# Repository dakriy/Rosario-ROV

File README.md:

# Rosario-ROV
This project is to create a working ROV with features such as live video for the WWU Rosario Beach Marine Laboratory.

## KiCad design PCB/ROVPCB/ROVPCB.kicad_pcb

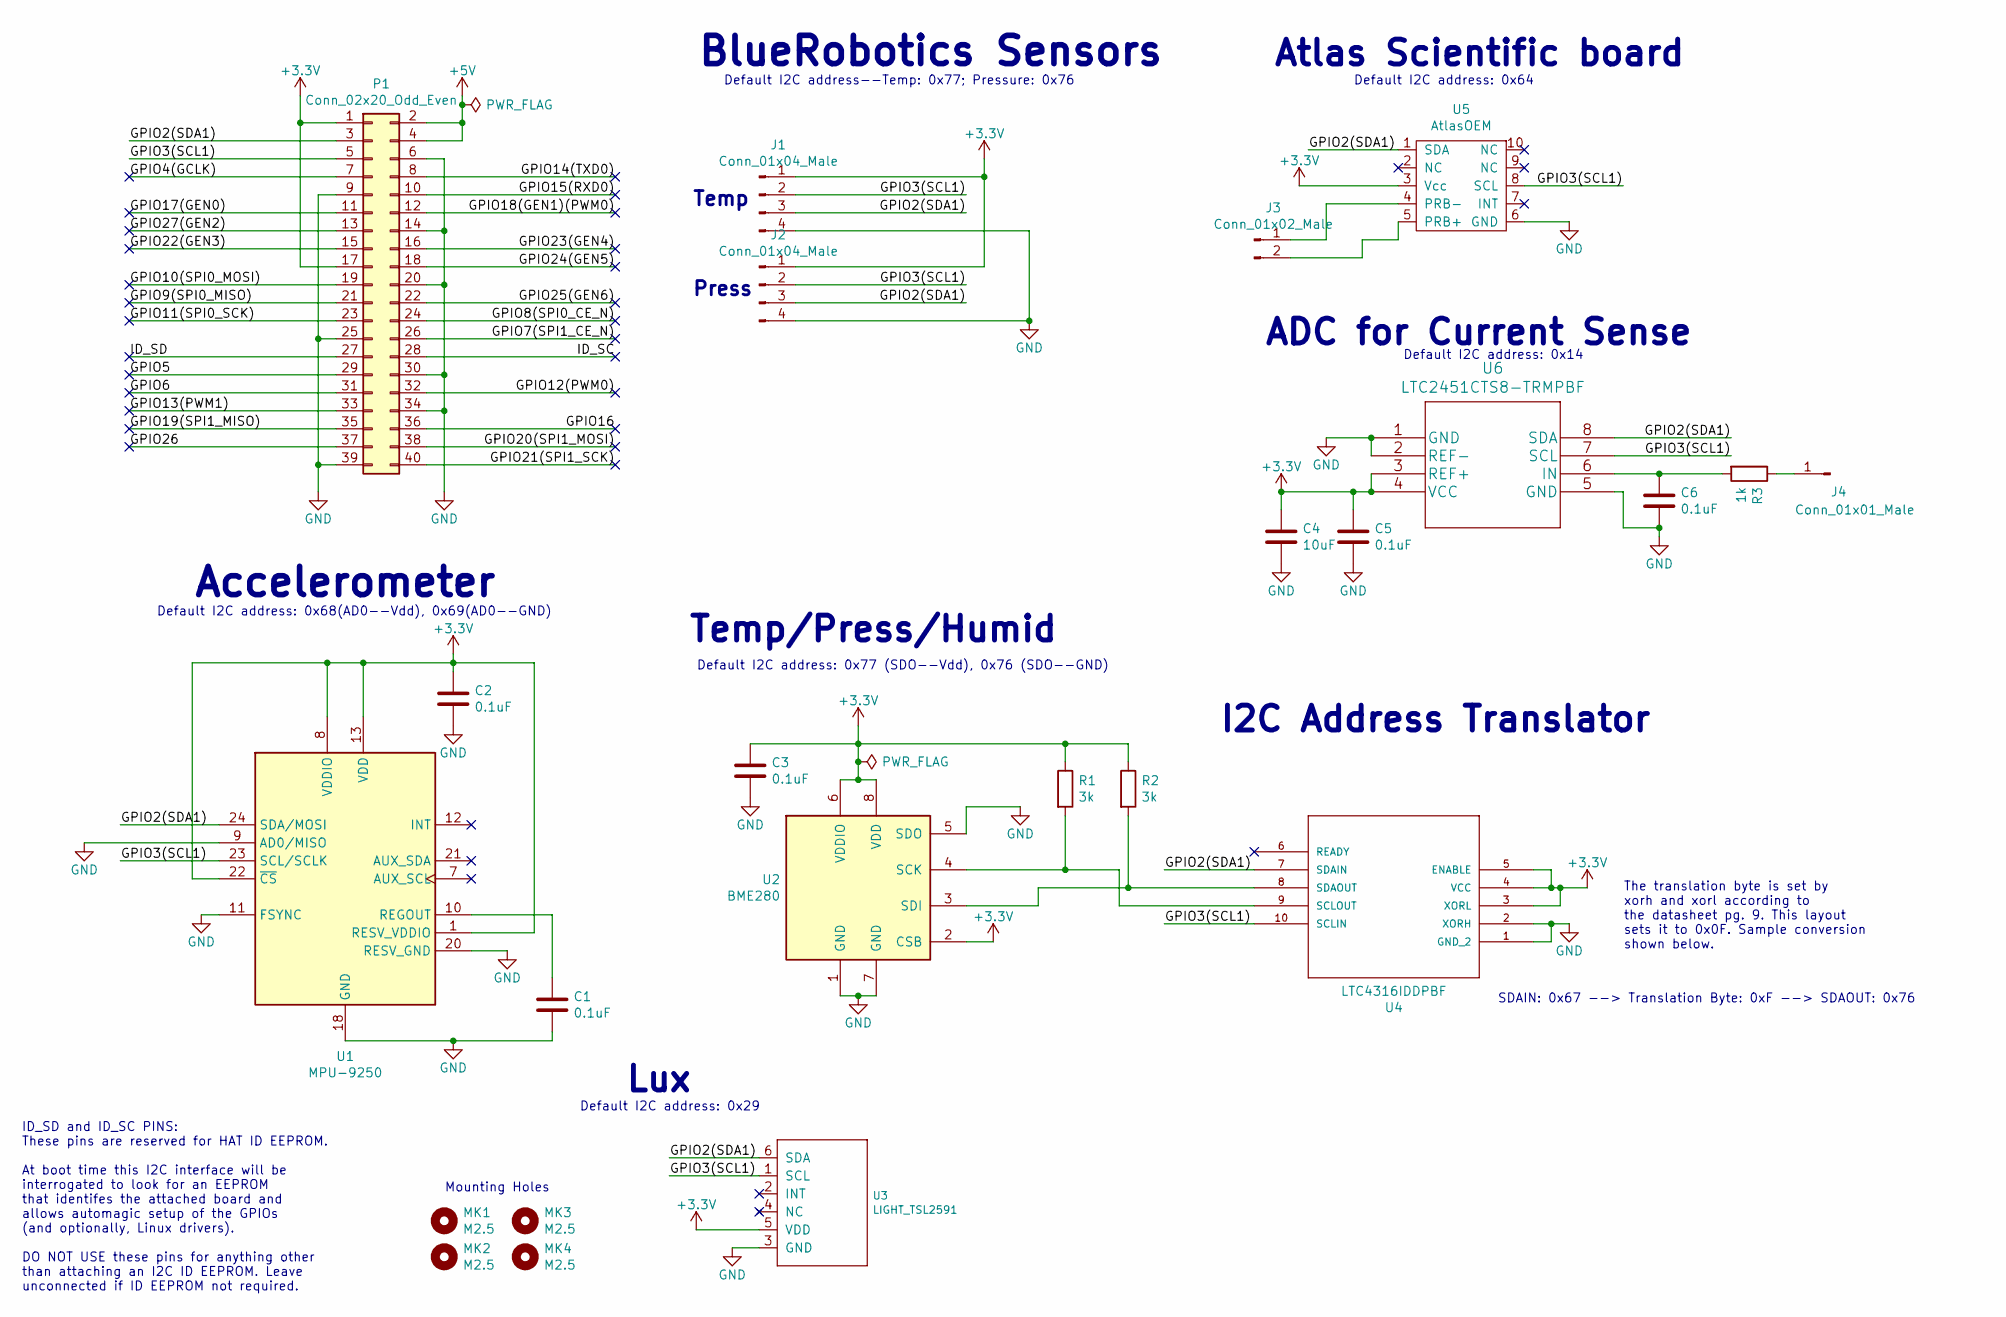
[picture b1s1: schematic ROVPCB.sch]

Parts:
C1, C2, C3, C5, C6: 0.1uF; C_0603_1608Metric
C4: 10uF; C_0603_1608Metric
J1, J2: Conn_01x04_Male; Hirose_DF13-04P-1.25DSA_1x04_P1.25mm_Vertical
J3: Conn_01x02_Male; SolderWirePad_1x02_P3.81mm_Drill0.8mm
J4: Conn_01x01_Male; SolderWirePad_1x01_Drill0.8mm
MK1, MK2, MK3, MK4: M2.5; MountingHole_2.7mm_M2.5
P1: Conn_02x20_Odd_Even; PinSocket_2x20_P2.54mm_Vertical
R1, R2: 3k; R_0805_2012Metric
R3: 1k; R_0805_2012Metric
U1: MPU-9250; InvenSense_QFN-24_3x3mm_P0.4mm
U2: BME280; Bosch_LGA-8_2.5x2.5mm_P0.65mm_ClockwisePinNumbering
U3: LIGHT_TSL2591; DFN6_TAOS
U4: LTC4316IDDPBF; MSOP-10_3x3mm_P0.5mm
U5: AtlasOEM; OEM Board
U6: LTC2451CTS8-TRMPBF

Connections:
+3V3: C2.1, C3.1, C4.1, C5.1, J1.1, J2.1, P1.1, P1.17, R1.1, R2.1, U1.1 (RESV_VDDIO), U1.8 (VDDIO), U1.13 (VDD), U1.22 (~CS), U2.2 (CSB), U2.6 (VDDIO), U2.8 (VDD), U3.5 (VDD), U4.3 (XORL), U4.4 (VCC), U4.5 (ENABLE), U5.3 (Vcc), U6.3 (REF+), U6.4 (VCC)
+5V: P1.2, P1.4
/GPIO2(SDA1): J1.3, J2.3, P1.3, U1.24 (SDA/MOSI), U3.6 (SDA), U4.7 (SDAIN), U5.1 (SDA), U6.8 (SDA)
/GPIO3(SCL1): J1.2, J2.2, P1.5, U1.23 (SCL/SCLK), U3.1 (SCL), U4.10 (SCLIN), U5.8 (SCL), U6.7 (SCL)
/GPIO4(GCLK): P1.7
/GPIO5: P1.29
/GPIO6: P1.31
/GPIO7(SPI1_CE_N): P1.26
/GPIO8(SPI0_CE_N): P1.24
/GPIO9(SPI0_MISO): P1.21
/GPIO10(SPI0_MOSI): P1.19
/GPIO11(SPI0_SCK): P1.23
/GPIO12(PWM0): P1.32
/GPIO13(PWM1): P1.33
/GPIO14(TXD0): P1.8
/GPIO15(RXD0): P1.10
/GPIO16: P1.36
/GPIO17(GEN0): P1.11
/GPIO18(GEN1)(PWM0): P1.12
/GPIO19(SPI1_MISO): P1.35
/GPIO20(SPI1_MOSI): P1.38
/GPIO21(SPI1_SCK): P1.40
/GPIO22(GEN3): P1.15
/GPIO23(GEN4): P1.16
/GPIO24(GEN5): P1.18
/GPIO25(GEN6): P1.22
/GPIO26: P1.37
/GPIO27(GEN2): P1.13
/ID_SC: P1.28
/ID_SD: P1.27
GND: C1.2, C2.2, C3.2, C4.2, C5.2, C6.2, J1.4, J2.4, P1.6, P1.9, P1.14, P1.20, P1.25, P1.30, P1.34, P1.39, U1.9 (AD0/MISO), U1.11 (FSYNC), U1.18 (GND), U1.20 (RESV_GND), U2.1 (GND), U2.5 (SDO), U2.7 (GND), U3.3 (GND), U4.1 (GND_2), U4.2 (XORH), U5.6 (GND), U6.1 (GND), U6.2 (REF-), U6.5 (GND)
unnamed: C1.1, U1.10 (REGOUT)
unnamed: C6.1, R3.2, U6.6 (IN)
unnamed: J3.1, U5.4 (PRB-)
unnamed: J3.2, U5.5 (PRB+)
unnamed: J4.1, R3.1
unnamed: R1.2, U2.4 (SCK), U4.9 (SCLOUT)
unnamed: R2.2, U2.3 (SDI), U4.8 (SDAOUT)

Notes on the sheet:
ID_SD and ID_SC PINS: These pins are reserved for HAT ID EEPROM. At boot time this I2C interface will be interrogated to look for an EEPROM that identifes the attached board and allows automagic setup of the GPIOs (and optionally, Linux drivers). DO NOT USE these pins for anything other than attach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
Mounting Holes
BlueRobotics Sensors
Accelerometer
Temp/Press/Humid
Lux
I2C Address Translator
Atlas Scientific board
SDAIN: 0x67 --> Translation Byte: 0xF --> SDAOUT: 0x76
The translation byte is set by xorh and xorl according to the datasheet pg. 9. This layout sets it to 0x0F. Sample conversion shown below.
Default I2C address: 0x77 (SDO--Vdd), 0x76 (SDO--GND)
Default I2C address: 0x68(AD0--Vdd), 0x69(AD0--GND)
Default I2C address: 0x29
Default I2C address: 0x64
Default I2C address--Temp: 0x77; Pressure: 0x76
ADC for Current Sense
Default I2C address: 0x14
Temp
Press

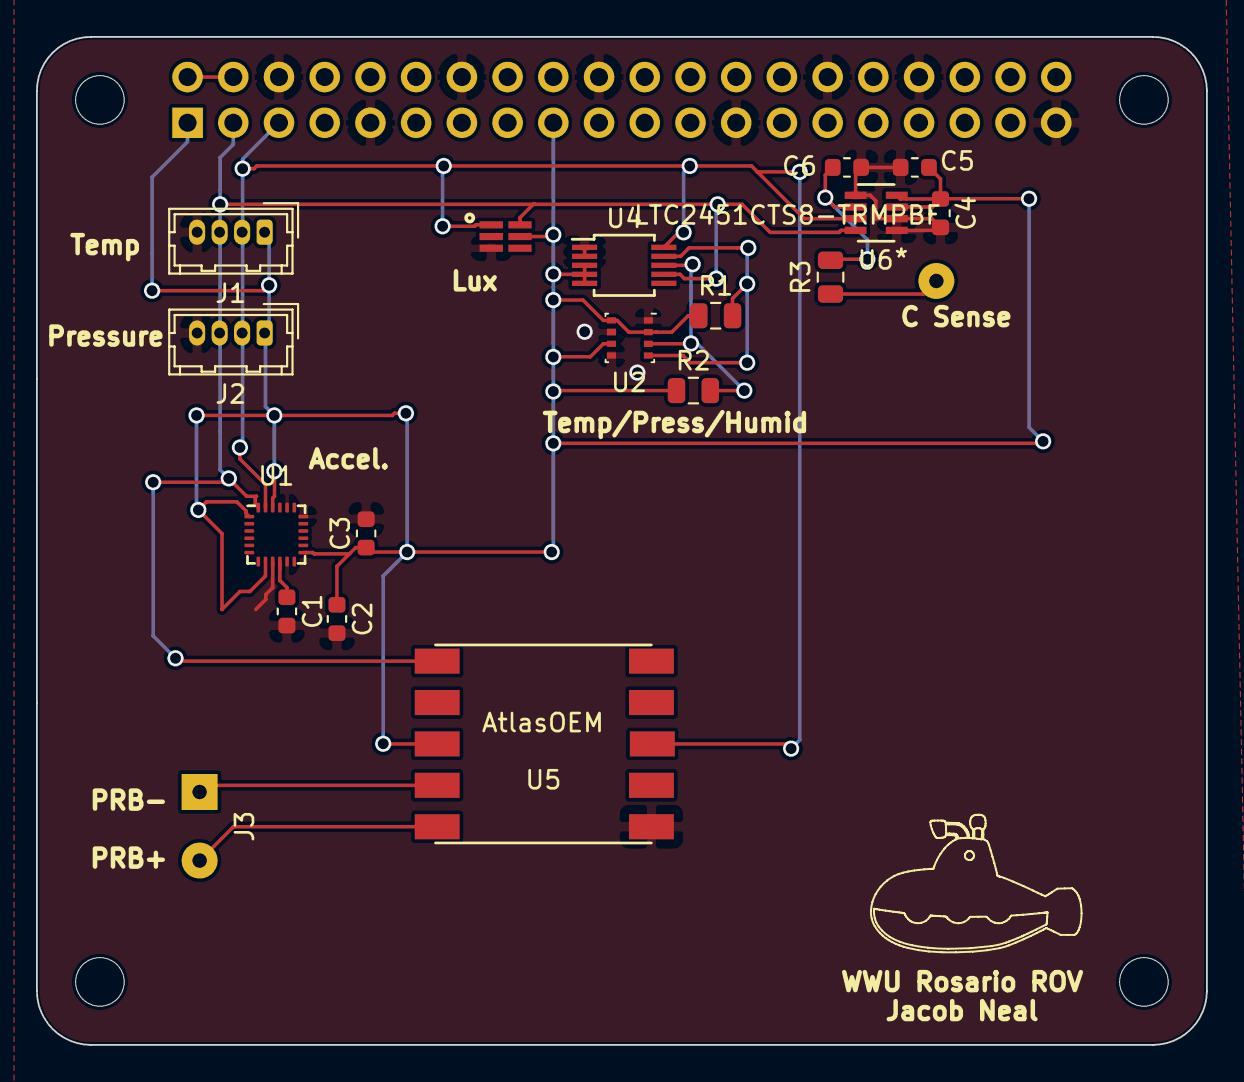
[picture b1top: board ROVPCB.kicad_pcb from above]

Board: 2 copper layers, 65.0 x 56.0 mm, 24 parts (1 on the bottom side), 12 nets.

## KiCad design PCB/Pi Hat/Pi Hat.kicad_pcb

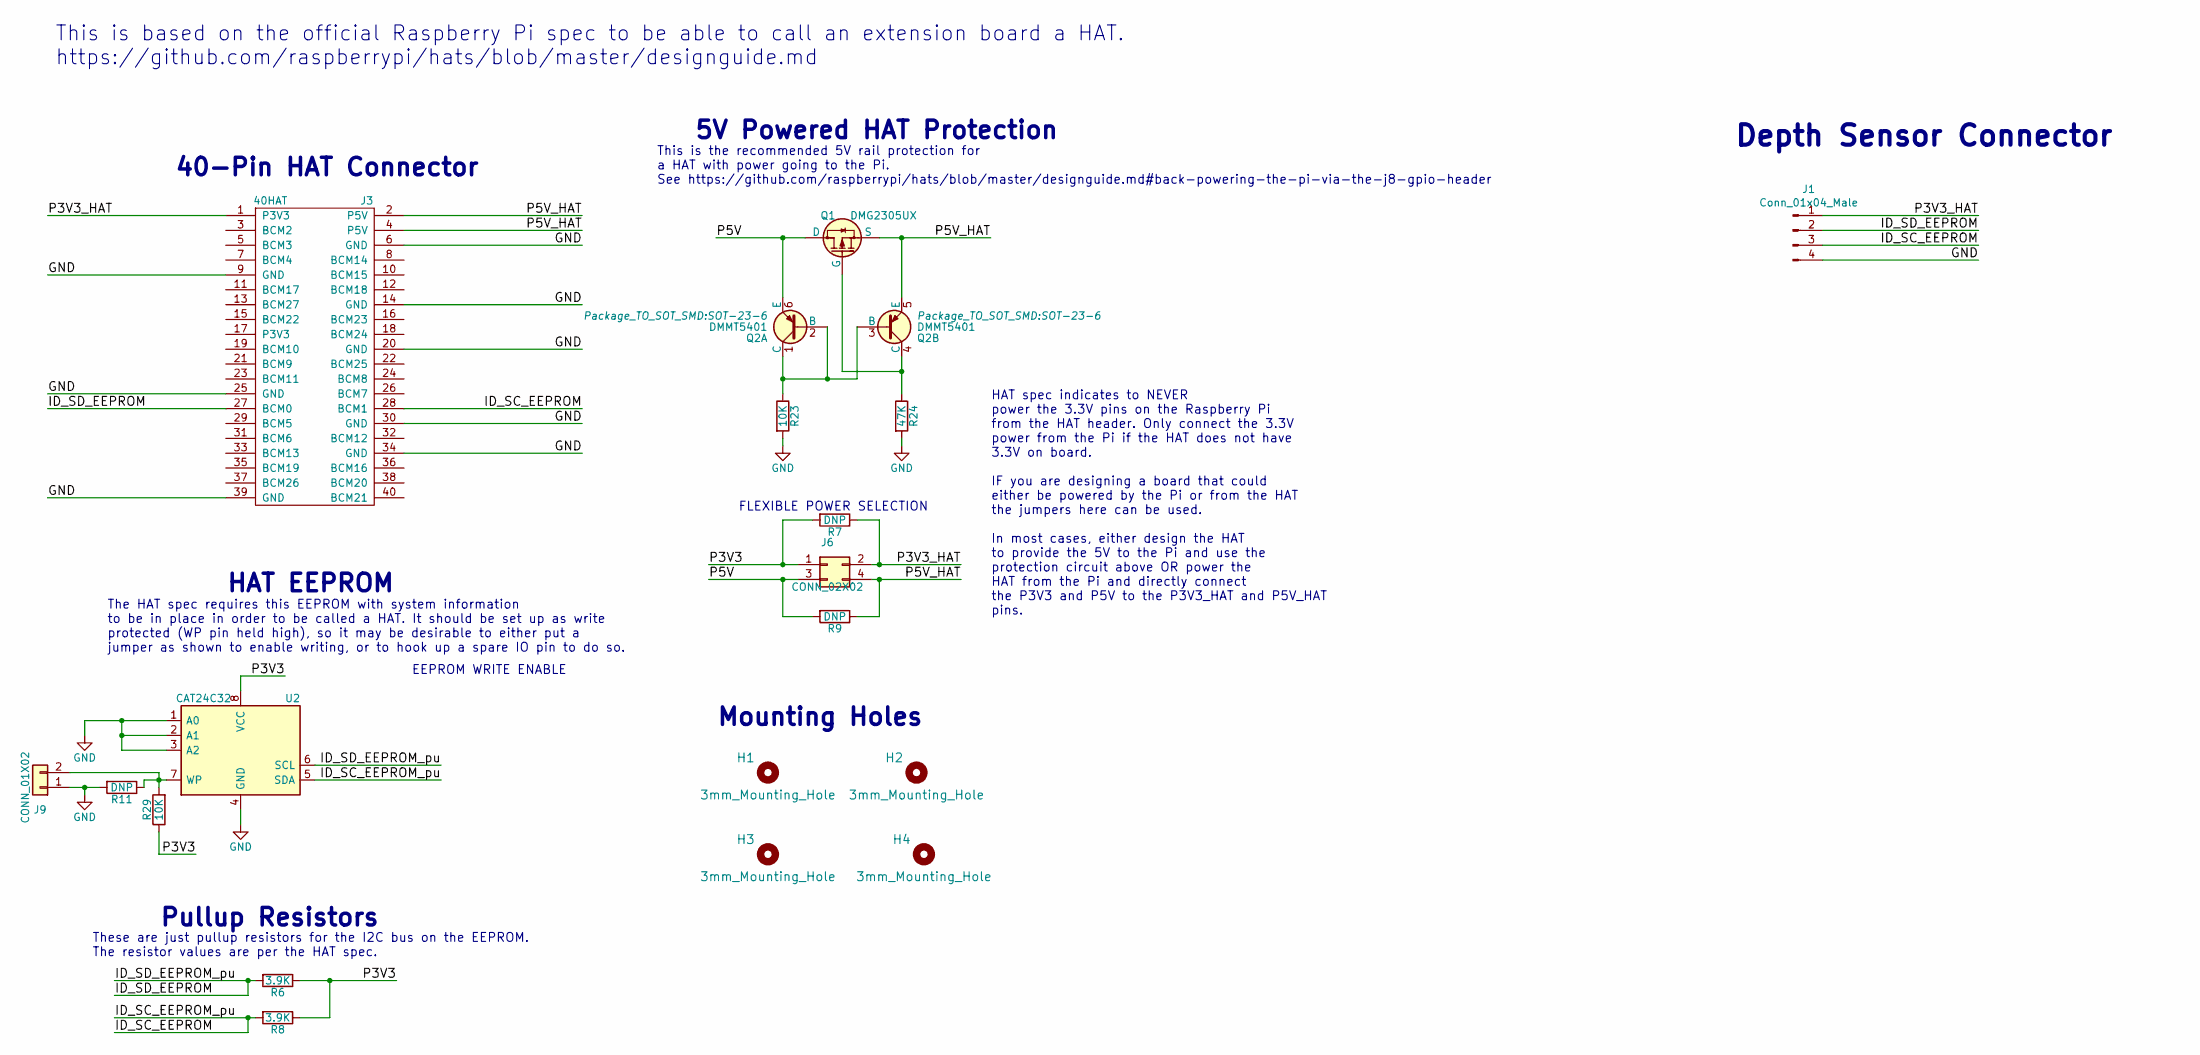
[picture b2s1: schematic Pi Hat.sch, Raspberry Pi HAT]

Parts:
H1, H2, H3, H4: 3mm_Mounting_Hole; NPTH_3mm_ID
J1: Conn_01x04_Male; Hirose_DF13-04P-1.25DSA_1x04_P1.25mm_Vertical
J3: 40HAT; PinSocket_2x20_P2.54mm_Vertical
J6: CONN_02X02; PinHeader_2x02_P2.54mm_Vertical
J9: CONN_01X02; PinHeader_1x02_P2.54mm_Vertical
Q1: DMG2305UX; SOT-23
Q2: DMMT5401; SOT-23-6
R6, R8: 3.9K; R_0603_1608Metric_Pad0.84x1.00mm_HandSolder
R7, R9, R11: DNP; R_0603_1608Metric_Pad0.84x1.00mm_HandSolder
R23, R29: 10K; R_0603_1608Metric_Pad0.84x1.00mm_HandSolder
R24: 47K; R_0603_1608Metric_Pad0.84x1.00mm_HandSolder
U2: CAT24C32; SOIC-8_3.9x4.9mm_P1.27mm

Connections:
/ID_SC_EEPROM: J1.3, J3.28 (BCM1), R8.2, U2.5 (SDA)
/ID_SD_EEPROM: J1.2, J3.27 (BCM0), R6.2, U2.6 (SCL)
/P3V3: J6.1, R6.1, R7.2, R8.1, R29.1, U2.8 (VCC)
/P3V3_HAT: J1.1, J3.1 (P3V3), J6.2, R7.1
/P5V: J6.3, Q1.3 (D), Q2.6 (E), R9.2
/P5V_HAT: J3.2 (P5V), J3.4 (P5V), J6.4, Q1.2 (S), Q2.5 (E), R9.1
GND: J1.4, J3.6 (GND), J3.9 (GND), J3.14 (GND), J3.20 (GND), J3.25 (GND), J3.30 (GND), J3.34 (GND), J3.39 (GND), J9.1, R11.2, R23.2, R24.2, U2.1 (A0), U2.2 (A1), U2.3 (A2), U2.4 (GND)
unnamed: J9.2, R11.1, R29.2, U2.7 (WP)
unnamed: Q1.1 (G), Q2.4 (C), R24.1
unnamed: Q2.1 (C), Q2.2 (B), Q2.3 (B), R23.1

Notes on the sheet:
FLEXIBLE POWER SELECTION
5V Powered HAT Protection
This is the recommended 5V rail protection for a HAT with power going to the Pi. See https://github.com/raspberrypi/hats/blob/master/designguide.md#back-powering-the-pi-via-the-j8-gpio-header
EEPROM WRITE ENABLE
Pullup Resistors
HAT EEPROM
Mounting Holes
40-Pin HAT Connector
HAT spec indicates to NEVER power the 3.3V pins on the Raspberry Pi from the HAT header. Only connect the 3.3V power from the Pi if the HAT does not have 3.3V on board. IF you are designing a board that could either be powered by the Pi or from the HAT the jumpers here can be used. In most cases, e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
The HAT spec requires this EEPROM with system information to be in place in order to be called a HAT. It should be set up as write protected (WP pin held high), so it may be desirable to either put a jumper as shown to enable writing, or to hook up a spare IO pin to do so.
These are just pullup resistors for the I2C bus on the EEPROM. The resistor values are per the HAT spec.
This is based on the official Raspberry Pi spec to be able to call an extension board a HAT. https://github.com/raspberrypi/hats/blob/master/designguide.md
Depth Sensor Connector

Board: 2 copper layers, 19 parts (1 on the bottom side), 10 nets, no tracks yet.

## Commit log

2018-11-29 Add the base files
2018-11-29 test
2018-11-29 Add gitignore for hte py cache
2018-11-29 Added module for tsys01 temperature sensor
2018-11-30 main.py Records measurements in /home/pi/Measurements
2018-11-30 Changed some redundancies and unecessary code in main.py
2018-11-30 Removed the unnecessary data txt files
2018-11-30 Stuff
2018-11-30 HAAANDS
2018-11-30 I AM MAKING COMMITS WITH MY HAAAAAAAAANDS
2018-12-06 Lastest changes after the test last weekend.
2019-02-08 Adding files for PCB Developement
2019-02-10 Add a boatload of code from another project that will be useful, also integrate imgui and sfml and get that working.
2019-02-10 Ignore imgui files
2019-02-10 Get main menu page thing working
2019-02-10 Fix the slight shifting in options because of a previous element that I have removed.
2019-02-10 Fix a bug when switching frames, IMGUI hates it because I haven't drawn or ended the frame before updating again on frame change. Also add a couple frames and refactor some things that were still aro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
2019-02-10 Start network talking. Got em going and searching on the broadcast address...
2019-02-11 Pinging works
2019-02-11 Broadcast script
2019-02-11 Commit while it still works before I screw everything up. Abstracted my event processor even more so that I can use it with custom events... what is wrong with me? Also start defining some more packe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
2019-02-11 YO IT WORKS, I didn't think my event handler port would work, but I guess it does... WOOT Hurray for template magic!
2019-02-11 Code
2019-02-11 Bug fixes and video experiments
2019-02-11 I hope this works
2019-02-11 ok time to switch to tcp
2019-02-11 Chagen to tcp hopefully?
2019-02-11 aTTrIbuTeERrOR: tyPE ObJECT 'SOcKEt' has NO AttribUtE 'SOl_SOCKeT'
2019-02-11 I found a better template to use. Has more america points.
2019-02-11 Small Changes to pcb to make it look nice.
2019-02-11 Added Accelerometer to schematic and Board.
2019-02-11 Testing for the branching process.
2019-02-11 Getting rid of testing stuff
2019-02-12 Commit something working before I forget...
2019-02-12 Changes on here
2019-02-12 Attempt to add pressure and temp stuff
2019-02-12 Attempt different way of sending video as a test.
2019-02-12 Oh that's exiciting... it all works lmao
2019-02-12 servo woo!
2019-02-12 idek
2019-02-12 Attempt at making servo work with joystick! Lets see how it goes!
2019-02-12 Couple changes but the servo works!
2019-03-18 Start on graphing functionality
2019-03-18 Scaling on the x axis works now, yay
2019-03-21 Got x and y lines working, still breaks if you zoom in or out too far.
2019-03-22 Start moving to cmake
2019-03-22 Builds with cmake on windows now. Cool
2019-03-23 Having trouble running debug with ucrtbased.dll.
2019-03-24 randomly works now. yay was getting some weird error in the sfml library when loading fonts in some system dll, but it just stopped.
2019-03-24 found and fixed that weird debug build bug! It was sometihng to do with using the wrong runtime libraries.
2019-03-26 Newest on the calculator
2019-03-26 Apply substringing to parse function tokens, also advance iterator
2019-03-26 initialize end offset tracker and remove an unnecessary space in a memcpy
2019-03-27 Scientific calculator works now for the most part and it's beautiful
2019-03-29 Actually throw a syntax error if we have one, also fix the negate operator.
2019-03-29 Fix equality case.
2019-03-30 Fix a typo
2019-03-30 Add equation type resolving for what type of graphing we can do
2019-03-30 Fix typo and add more math functionality and fix a typo and a missing parenthesis
2019-03-30 Now fix the typo and get basic y=function of x graphing working! it looks nice!
2019-03-30 use fmin and fmax becuase we are using this with floating point numbers and I want full floating point functionality
2019-04-01 Expression copying done
2019-04-02 Continue porting code to the dedicated grapher class
2019-04-03 Finish port to grapher and only use setVertialSyncEnabled and not setFramerateLimit.
2019-04-04 Add way to tell if an equation has an equals sign or not and caluclate it on the main screen if it does not have an equals sign.
2019-04-05 Finish port to grapher.
2019-04-05 Start doing marching squares
2019-04-08 MARCHING SQUARES WORKS THANKS DUSTIN AND LUCAS THEY HELPED SOME DEBUGGING AT THE END WITH SPIKES.
2019-04-08 update imgui
2019-04-08 Fix grapher for real. Had an off by 1 error when indexing grid on the row size.
2019-04-08 Fix bug with expression not looking at the equation flag and also change some default marching squares parameters.
2019-04-11 Get the build working on linux
2019-04-11 Start recreating ROV app
2019-04-13 Modify gitignores
2019-04-14 Start ROV application rewrite, get base networking code.
2019-04-14 Make it build on windows under VS and get broadcasting working correctly
2019-04-14 Refactor boatside application to use packets and get packet sending working correctly.
2019-04-15 Get ping packets working. Need to rewrite top side networking cause its done badly cause I did it at 4 AM before my presentation. It worked tho
2019-04-16 Filling in Display cutout on PCB
2019-04-16 New accelerometer and added the Humdity/Temp/Pressure Sensor
2019-04-16 Add coordinate conversion helper
2019-04-17 Added all the things
2019-04-17 HouseKeepinggit add *
2019-04-17 Added I2C Address Translator
2019-04-17 Start rewrite of network library swiching computers for a sec
2019-04-18 Make boatside network application multithreaded.
2019-04-22 Added I2C addresses to schematic and other housekeeping stuff
2019-04-22 Adding the Atlas Board... BNC??
2019-04-22 BNCgit add * Boiz
2019-04-22 NO BNC! YASSS
2019-04-22 Pullup resistors in between translater and humidity sensor
2019-04-23 Rewrite networking on the ROV to be like the Controller for consistency, also it was done better. Ready to start doing data logging now! Ok next up is getting the main time thread going on the ROV.
2019-04-24 I dont have time
2019-04-24 Fixed DRC errors and other things
2019-04-24 I think it is done!
2019-04-24 MAOR Changes
2019-04-24 Refactor and move things. Figured out how to do data transfer.
2019-04-24 Added Solder Stencil Layer
2019-04-25 Generated Gerber files
2019-04-25 Nothing added just generating Gerbs
2019-04-25 Added a cute little submarine logo
2019-04-25 Start ROV Sensor side code
2019-04-25 Fix references to the new SensorInfo
2019-04-25 Start moving to unique ptrs and also figure out network info data stuff
2019-04-25 Added some documentation stuffs
2019-04-25 Move more htings over to smart pointers so I don't have to worry about memory management.
2019-04-26 Use tabs in some files instead of 4 spaces
2019-04-26 Get rid of warnings and start redoing network packets
2019-04-26 Start setting up packets for sensor information reqests.
2019-04-27 Don't interact with app when the user is trying to do things with ImGui
2019-04-27 Reuse some code that I can.
2019-04-27 Make function parameter const, for wider useable code.
2019-04-27 Annotate with override
2019-04-28 Make a debug logger
2019-04-28 Make the app logger multithreaded
2019-04-28 Very WIP
2019-04-28 Migrating to pi
2019-04-28 Build changes.
2019-04-28 Minimum cmake version for c++17
2019-04-29 I hate segfaults... So much...
2019-04-29 atmoic bool things? idk
2019-04-30 Fixed the stupid segfault... I'm actually retarded. Idk how I have come this far.
2019-04-30 I can talk the pressure sensor's language!
2019-04-30 Sensor data is next.
2019-05-01 Pressure readings work great now!
2019-05-01 Start porting lux sensor
2019-05-02 Light sensor works now too. First try no debugging needed!
2019-05-02 Port temperature libraries over. Worked on first try! No debugging!
2019-05-03 Adding mas Documentation
2019-05-05 Moderinze cmake a bit. CMAKE IS SO AGGRIVATING. It didn't work for hours, and then it just randomly worked without me really changing anything. UGH
2019-05-05 Kind of got video working a little bit...
2019-05-05 Compress video before sending it over the network. Video works great now at like 15fps
2019-05-06 Add time synchronization.
2019-05-06 switching computers
2019-05-06 Fix lock not getting unlocked in certian situations causing a deadlock in the network.
2019-05-06 add an option to connect to the default IP
2019-05-06 Generalize engine, add updateable entities to it.
2019-05-06 Mission window
2019-05-06 Add tooltips for imgui, and also don't add devices multiple times.
2019-05-07 Get basic data recording working.
2019-05-07 Some stuff missed the last commit.
2019-05-07 Add dynamic data graphing and fix graph zoom slightly.... Graph navigation controls still need a lot of help.
2019-05-07 Improve timing accuracy and also actually use the requested frequency.
2019-05-07 Projector spazz fix.
2019-05-07 Add internal pressure/temp/humidity sensors and fix sensor selecting code
2019-05-07 Initialize variable.
2019-05-07 Start attempting to get servos working.
2019-05-07 cast var
2019-05-07 UsE aUTo
2019-05-07 disable imgui demo window for now
2019-05-10 Trying to get first servo working. Something is weird with timings somewhere. Can't find out where. Need to look at the output wave to see if I'm outputting the correct thing. Bed time now. Good nigh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
2019-05-10 Midpoint is actually closer to 6.5
2019-05-11 FRIGGIN PERCENTAGES. Apparently, i DoN't KnOw HoW pErCeNtAgEs WoRk. I seriously, messed up... how percentages work... for like 2 days straight... 5 times in a row... I have no words to describe my st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
2019-05-13 Accidently removed an include that was needed.
2019-05-14 Stupid GERBSgit add *!
2019-05-21 Stupid i2c inputs were flipped.....
2019-05-21 The correct footprint.... DUMB
2019-05-25 CHanges on this so far
2019-05-25 A few minor changes based on testing.
2019-05-26 Add second servo and light control
2019-05-26 Working on Linux
2019-05-26 conductivity... wooooo, also magic record button.
2019-05-26 Well that was a really big and stupid bug, I gotta completely overhaul the sensor information transfer thing... its awful right now....
2019-05-27 Logging onboard done since we cannot do live tomorrow anyway. RIP.
2019-05-27 Temperature compensation for conductivity.
2019-06-10 Added BOM
2019-06-27 Code cleanup and added a couple features on ROV side.
2019-06-27 Make it so ROV can keep recording data even after disconnect. Also implement full ROV state machine.
2019-06-27 Update statistic settings in case anybody in the future is using this jetbrains plugin...
2019-06-28 Get file transfer and managmement working for summer research
2019-06-28 Add using current time as an option for filename. Also fix bug where it'd crash if the mission data folder didn't exist
2019-06-29 Add an icon
2019-07-10 Hard code aboslute path for the raspberry pi

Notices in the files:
parts and their libraries:
Copyright 2016 Accelerated Designs. All rights reserved.
